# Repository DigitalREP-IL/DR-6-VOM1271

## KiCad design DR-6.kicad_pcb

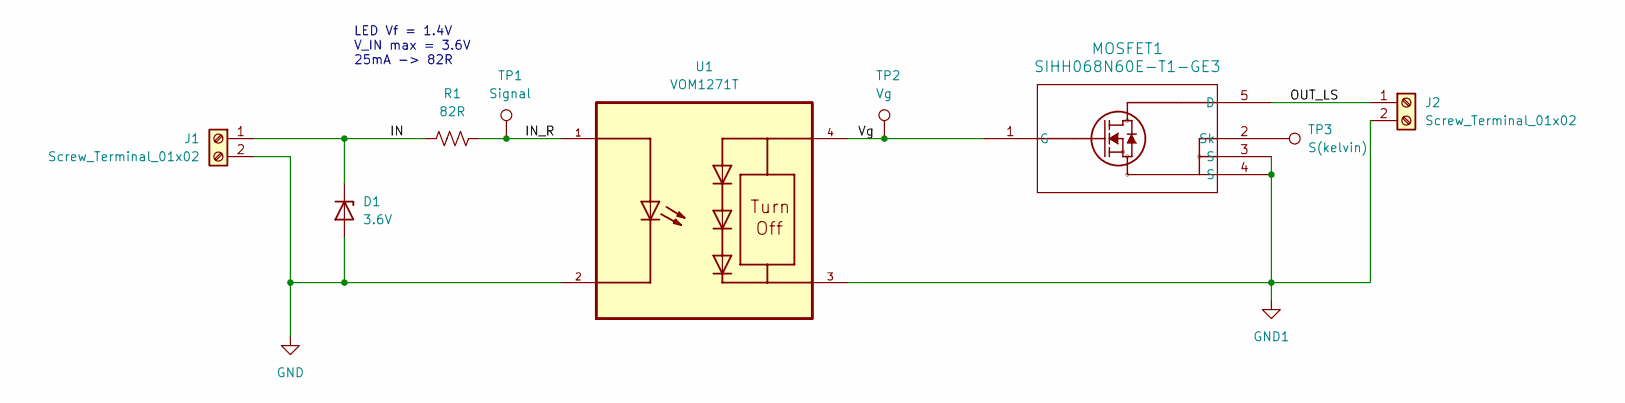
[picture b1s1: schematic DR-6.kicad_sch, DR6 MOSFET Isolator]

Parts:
D1: 3.6V; D_SMF
J1, J2: Screw_Terminal_01x02; TerminalBlock_TE_282834-2_1x02_P2.54mm_Horizontal
MOSFET1: SIHH068N60E-T1-GE3; PPAK8X8_VIS
R1: 82R; R_0603_1608Metric
TP1: Signal; TestPoint_THTPad_1.5x1.5mm_Drill0.7mm
TP2: Vg; TestPoint_THTPad_1.5x1.5mm_Drill0.7mm
TP3: S(kelvin); TestPoint_THTPad_1.5x1.5mm_Drill0.7mm
U1: VOM1271T; SOIC254P695X242-4N

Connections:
/IN: D1.1 (K), J1.1, R1.1
/IN_R: R1.2, TP1.1, U1.1
/OUT_LS: J2.1, MOSFET1.5 (D)
/Vg: MOSFET1.1 (G), TP2.1, U1.4
GND: D1.2 (A), J1.2, U1.2
GND1: J2.2, MOSFET1.3 (S), MOSFET1.4 (S), U1.3
unnamed: MOSFET1.2 (Sk), TP3.1

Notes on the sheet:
LED Vf = 1.4V V_IN max = 3.6V 25mA -> 82R

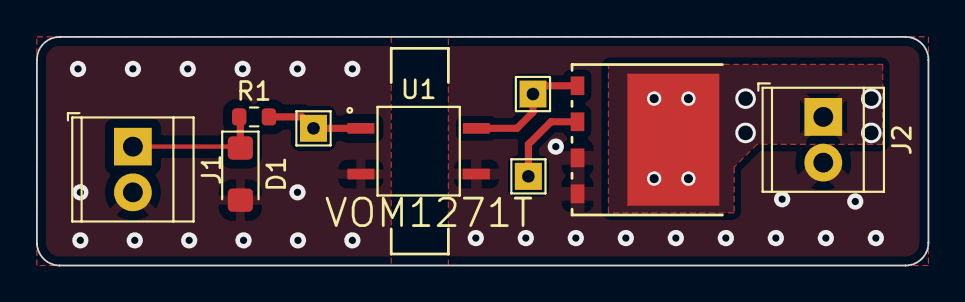
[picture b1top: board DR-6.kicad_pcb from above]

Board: 2 copper layers, 49.5 x 12.7 mm, 9 parts (0 on the bottom side), 7 nets.

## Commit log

2024-03-20 Initial Commit of WIP
